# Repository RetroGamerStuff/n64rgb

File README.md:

# N64 RGB 

A collection of RGB mods for the N64. This repository includes:

- a simple RGB amp
  * based on TI's video amplifier THS7374 / THS7373 (only for some NTSC-units)
  * folder: simpleRGBAmp
- a general RGB digital-to-analog converter based on viletims schematics
  * supported devices: MaxII (EPM240T100C5, EPM570T100C5) and MaxV (5M240ZT100C4, 5M570ZT100C4) CPLDs
  * PCB files (common for all supported devices) and firmware (separate programming files) are provided
  * folder: generalRGBmod
- an advanced RGB digital-to-analog converter with optional YPbPr conversion
  * supported FPGA: Cyclone IV EP4CE10E22 and Cyclone 10 LP 10CL010YE144
  * PCB files (common for all supported devices) and firmware (separate programming files) are provided
  * additional Filter board for the outputted video signal if you need that
  * folder: advancedRGBmod
- additional RCP-NUS Adapter (flexible PCB):
  * buffering of video signals for N64RGB/N64Adv installs with wires
  * PCB files provided
  * folder: misc/RCP2Pads
- additional RCP-NUS to N64RGBv2.1/N64Adv install adapter (long flexible PCB):
  * buffering of video signals for N64RGBv2.1/N64Adv
  * can be directly connected to modding board
  * PCB files provided
  * folder: misc/RCP2N64RGB
- Filter AddOn for N64RGBv2 and N64 Advanced:
  * used to filter the video signal comming out of the ADV7125 or to adjust signal levels such that one can use SNES PAL RGB cables
  * PCB files provided
  * folder: misc/FilterAddOn
- Filter AddOn as flexible PCB for N64RGBv2.1 and N64 Advanced:
  * used to filter the video signal comming out of the ADV7125 or to adjust signal levels such that one can use SNES PAL RGB cables
  * PCB files provided
  * folder: misc/N64RGB2MoutFilter
- additional power supply PCB for viletime N64RGB DAC and N64RGBv1
  * PCB files provided
  * folder: misc/PowerReg

## Acknowledgement

Of course, many thanks to viletim for his initial CPLD-based DAC project, for providing a valuable commercial modding board as well as for publishing the schematics and source codes for that project.
I also want to send many thanks to Ikari_01. He has written the code to detect 480i and PAL/NTSC output with the CPLD. He provides a source code for the XC9572XL, which can be accessed here: [URL to Ikari_01's GitHub repository](https://github.com/mrehkopf/n64rgb)
Last but not least, thank you to Bob for his website [RetroRGB](http://retrorgb.com) and especially in this context here for collecting and sharing all the [RGB information regarding the N64](http://retrorgb.com/n64.html).

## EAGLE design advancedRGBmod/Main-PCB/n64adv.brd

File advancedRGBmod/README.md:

# Advanced N64 RGB Digital-to-Analog Mod

This folder contains all you need for a complete DIY RGB mod.

Please don't ask me for selling a modding. I either sell some prototypes on some forums marketplaces (which is very unlikely) or I don't have any of the boards.
This is a complete DIY modding project. So everybody is on his own here.

**WARNING:** This is an advanced DIY project if you do everything on your own. You need decent soldering skills. The FPGA has 0.5mm fine pitch with 144pins and one exposed pad below the IC, which has to be soldered to the PCB. Next to it the video DAC has also 0.5mm pin pitch on the board there are some SMD1206 resistor and ferrit bead arrays.

## Features

- Supporting for different FPGAs [1] on a common PCB design:
  * Cyclone IV EP4CE10E22
  * Cyclone 10 LP 10CL010YE144
- Video DAC ADV7125 (or ADV7123)
- Detection of 240p/288p vs. 480i/576i together with detection of NTSC vs. PAL mode
- VI-DeBlur in 240p/288p (horizontal resolution decreased from 640 to 320 pixels)
- 15bit color mode
- IGR features:
  * reset the console with the controller
  * full control on de-blur and 15bit mode with the controller
- Advanced features:
  * output of RGsB or YPBPr on demand
  * linedoubling of 240p/288p video to 480p/576p
  * linetrippling of 240p to (pseudo) 720p (NTSC content only, generated resolution is not a standard resolution so compatibility highly depends on your TV)
  * Bob de-interlace of 480i/576i to 480p/576p (with optional field shift fix (reduces vertical flicker))
  * configurable hybrid scanlines
  * Dejitter for PAL in LineX2 mode [2]
  * possible VGA output [3]
  * on-screen menu for configuration

The following shortly describes the main features of the firmware and how to use / control them.

#### Notes
##### [1]
For now, support for 6k LEs FPGAs (EP4CE6E22 and 10CL006YE144) has been discontinued. They are to small for an OSD menu implementation due to the small amount of block RAM. I will try to get it fit in future.

##### [2]

Experimental feature which might not be compatible with all PAL games. Please report incompatibilities on GitHub!

##### [3]

Not available if the filter adddon is used as HSYNC and VSYNC are shared outputs with F1 and F2 (filter selection)

### In-Game Routines (IGR)

Three functunalities are implemented: toggle de-blur feature / override heuristic for de-blur and toggle the 15bit mode (see above) as well as resetting the console.

The button combination are as follows:

- open on-screen menu: D-pad ri + L + R + C-ri
- reset the console: Z + Start + R + A + B (must be enabled in menu)
- (de)activate vi-deblur: (must be enabled in menu, see description above)
  - deactivate: Z + Start + R + C-le
  - activate: Z + Start + R + C-ri
- (de)activate 15bit mode: (must be enabled in menu, see description above)
  - deactivate: Z + Start + R + C-up
  - activate: Z + Start + R + C-dw

_Final remark on IGR_:  
However, as the communication between N64 and the controller goes over a single wire, sniffing the input is not an easy task (and probably my solution is not the best one). This together with the lack of an exhaustive testing (many many games out there as well my limited time), I'm looking forward to any incomming issue report to furhter improve this feature :)

### LowRes.-Deblur (VI-DeBlur)

VI-DeBlur of the picture information is only performed in 240p/288p. This is be done by simply blanking every second pixel. Normally, the blanked pixels are used to introduce blur by the N64 in 240p/288p mode. However, some games like Mario Tennis, 007 Goldeneye, and some others use these pixel for additional information rather than for blurring effects. In other words this means that these games uses full horizontal resolution even in 240p/288p output mode. Hence, the picture looks more blurry in this case if vi-deblur feature is activated.

The default state (whether vi-deblur is enabled for 240p/288p content or not) can be set in the menu.

### 16bit Color Mode

The 16bit color mode reduces the color depth from 21bit (7bit for each color) downto 16bits (5bit for red and blue, 6bit for green). Some very few games processes the color information in 16bit. The 16bit color mode simply sets LSBs to '0'.

- By default the 16bit mode is *off*! The default is set on each power cycle but not on a reset. Default can be switched in menu.
- to deactivate 16bit mode press Z + Start + R + C-up. (quick access function must be enabled in menu)
- to (re)activate 16bit mode press Z + Start + R + C-dw. (quick access function must be enabled in menu)

### Low Pass Filtering of the Video Output

The video DAC does not use any filtering. In general, this is also not needed. If you need DAC post-filtering though (receiver has a ADC build without any pre-filtering), you can install the filter addon (also provided in this repository).

The filter addon is based on a THS7368, where the video channels with selectable filter are used. As the filter is selected over the same pins as HSYNC and VSYNC, the addon is not compatible to VGA.

## Technical Information

A complete installation and setup guide to this modding kit is provided in the main folder of the repository. Here are some additional short notes.

### Checklist: How to build the project

- Use PCB files to order your own PCB or simply use the shared project(s) on OSHPark
- Source the components you need, e.g. from Mouser or Digikey
- Wait for everything to arrive
- Assemble your PCB
- Set all jumpers
- Flash the firmware to the serial flash device either in advanced (e.g. using the MiniPro) or after installation (e.g. using an Altera USB Blaster)
  * In advanced:
    * use the n64adv\__fpga-device_\_spi.bin binary
    * If your programmer does not support the serial flash  device on the N64Adv board (currently IS25LP016D), you may setup the flash program for another compatible device (e.g. A25L016 @SOP8). You may have to uncheck _Check ID_ options (or similar)
  * After installing:
    * Use the JIC programming file named n64adv\__fpga-device_.jic
    * Using the IntelFPGA programmer, JTAG chain is initialized by loading JIC file
    * N64 needs to be powered for flashing
    * Power cycle the N64 after flashing

### Jumpers

**IMPORTANT NOTE**  
Most jumpers are used as fallback if the software is unable to load a valid configuration from flash device U5. They were introduced on the modding board before a menu was in the firmware.  
The only exception is J1.2 - this jumper is still used to show the software whether the _Filter AddOn_ is installed or not.

There are some jumpers spreaded over the PCB, namely _J1_, _J2_, _J3_, _J4_, _J5_ and _J6_. _J1 - J4_ have to parts, let's say _.1_ and _.2_, where _.1_ is marked with the _dot_ on the PCB.

#### J1 (Filter AddOn)
##### J1.1 
- opened: output HSYNC and VSYNC for possible VGA output
- closed: use filter addon

##### J1.2
- opened: use filter of the addon board
- closed: bypass filter (actually filter is set to 95MHz cut-off which is way above the video signal content)

#### J2 (RGB, RGsB, YPbPr)
##### J2.1
- opened: RGB output
- closed: RGsB output (sync on green)

##### J2.2
- opened: RGB / RGsB output
- closed: YPbPr output (beats J2.1)

#### J3 (Scanline)
##### J3.1/J3.2
- opened / opened: 0%
- opened / closed: 25%
- closed / opened: 50%
- closed / closed: 100%

#### J33 (CSYNC level @ _/CS (75ohm)_ pad)

- opened: appr. 1.87V @ 75ohm termination i.e. needs a resistor inside the sync wire further attenuating the signal. Designed to work for cables with 470 ohm resistor inside resulting in appr. 450mV @ 75ohm termination
- closed: appr. 300mV @ 75ohm termination suitable for pass through wired cables at sync, works with standard TV / scaler setup

#### J4 (Linemode)
##### J4.1
- opened: linedoubling of 240p/288p to 480p/576p
- closed: no-linedoubling (beats J4.2)

##### J4.2
- opened: no bob de-interlace of 480i/576i
- closed: bob de-interlace of 480i/576i to 480p/576p (J4.1 must be opened)

#### J5
_J5_ is the JTAG connector.

#### J6 (_Outdated_; Power supply of analog outputs)
The analog part can be power with **either** 3.3V **or** 5V. If you want to power this part of the PCB with 3.3V, close _J6_ and leave pad _5V_ unconnected. If you want to power this part with 5V, leave _J6_ opened and connect pad _5V_ to +5V power rail of the N64. **NEVER connect 5V and close J6.**

#### Fallback Mode

A fallback mode can be activated by holding reset button down while powering on the N64. In the fallback mode **linedoubling and component conversion is turned off**. Sync on G/Y output is still on if one J2.1 or J2.2 is set as it does not affect RGBS.

### Source the PCB

Choose the PCB service which suits you. Here are some:

- OSHPark: [Link to the Main PCB](https://oshpark.com/shared_projects/Xo6yoQwD) (If the PCB was updated and I forgot to update this link, look onto [my profile](https://oshpark.com/profiles/borti4938))
- PCBWay.com: [Link](http://www.pcbway.com/), [Affiliate Link](http://www.pcbway.com/setinvite.aspx?inviteid=10658)

### Part List for the PCB

This part list a recommendation how the PCB is designed. If you are able to find pin-compatible devices / parts, you can use them.

#### Components

Components are listed in advancedRGBmod/Main-PCB/BOM_n64advanced.xlsx

### Firmware
The firmware is located in the folder firmware/. To build the firmware on your own you need Quartus Prime Lite (any version which supports Cyclone IV and 10 LP devices).

If you only want to flash the firmware, the configuration files are pre-compiled and located in firmware/output_files. You need the JIC appropriate for the FPGA you opted for (look for the *\_extension*).

For flashing you need:

- Altera USB Blaster
- Standalone Quartus Prime Programmer and Tools

#### Firmware Revision Numbering

- 1.0: initially commited version
- 2.0 (HDL) / 1.0 (SW): initial version with OSD driven menu
- HDL got a fallback to v. 1.xx from 2.0 after a while

#### Road Map / New Ideas

- return of vi-deblur heuristic
- test screen
- some more menu stuff

Any other ideas: email me :)

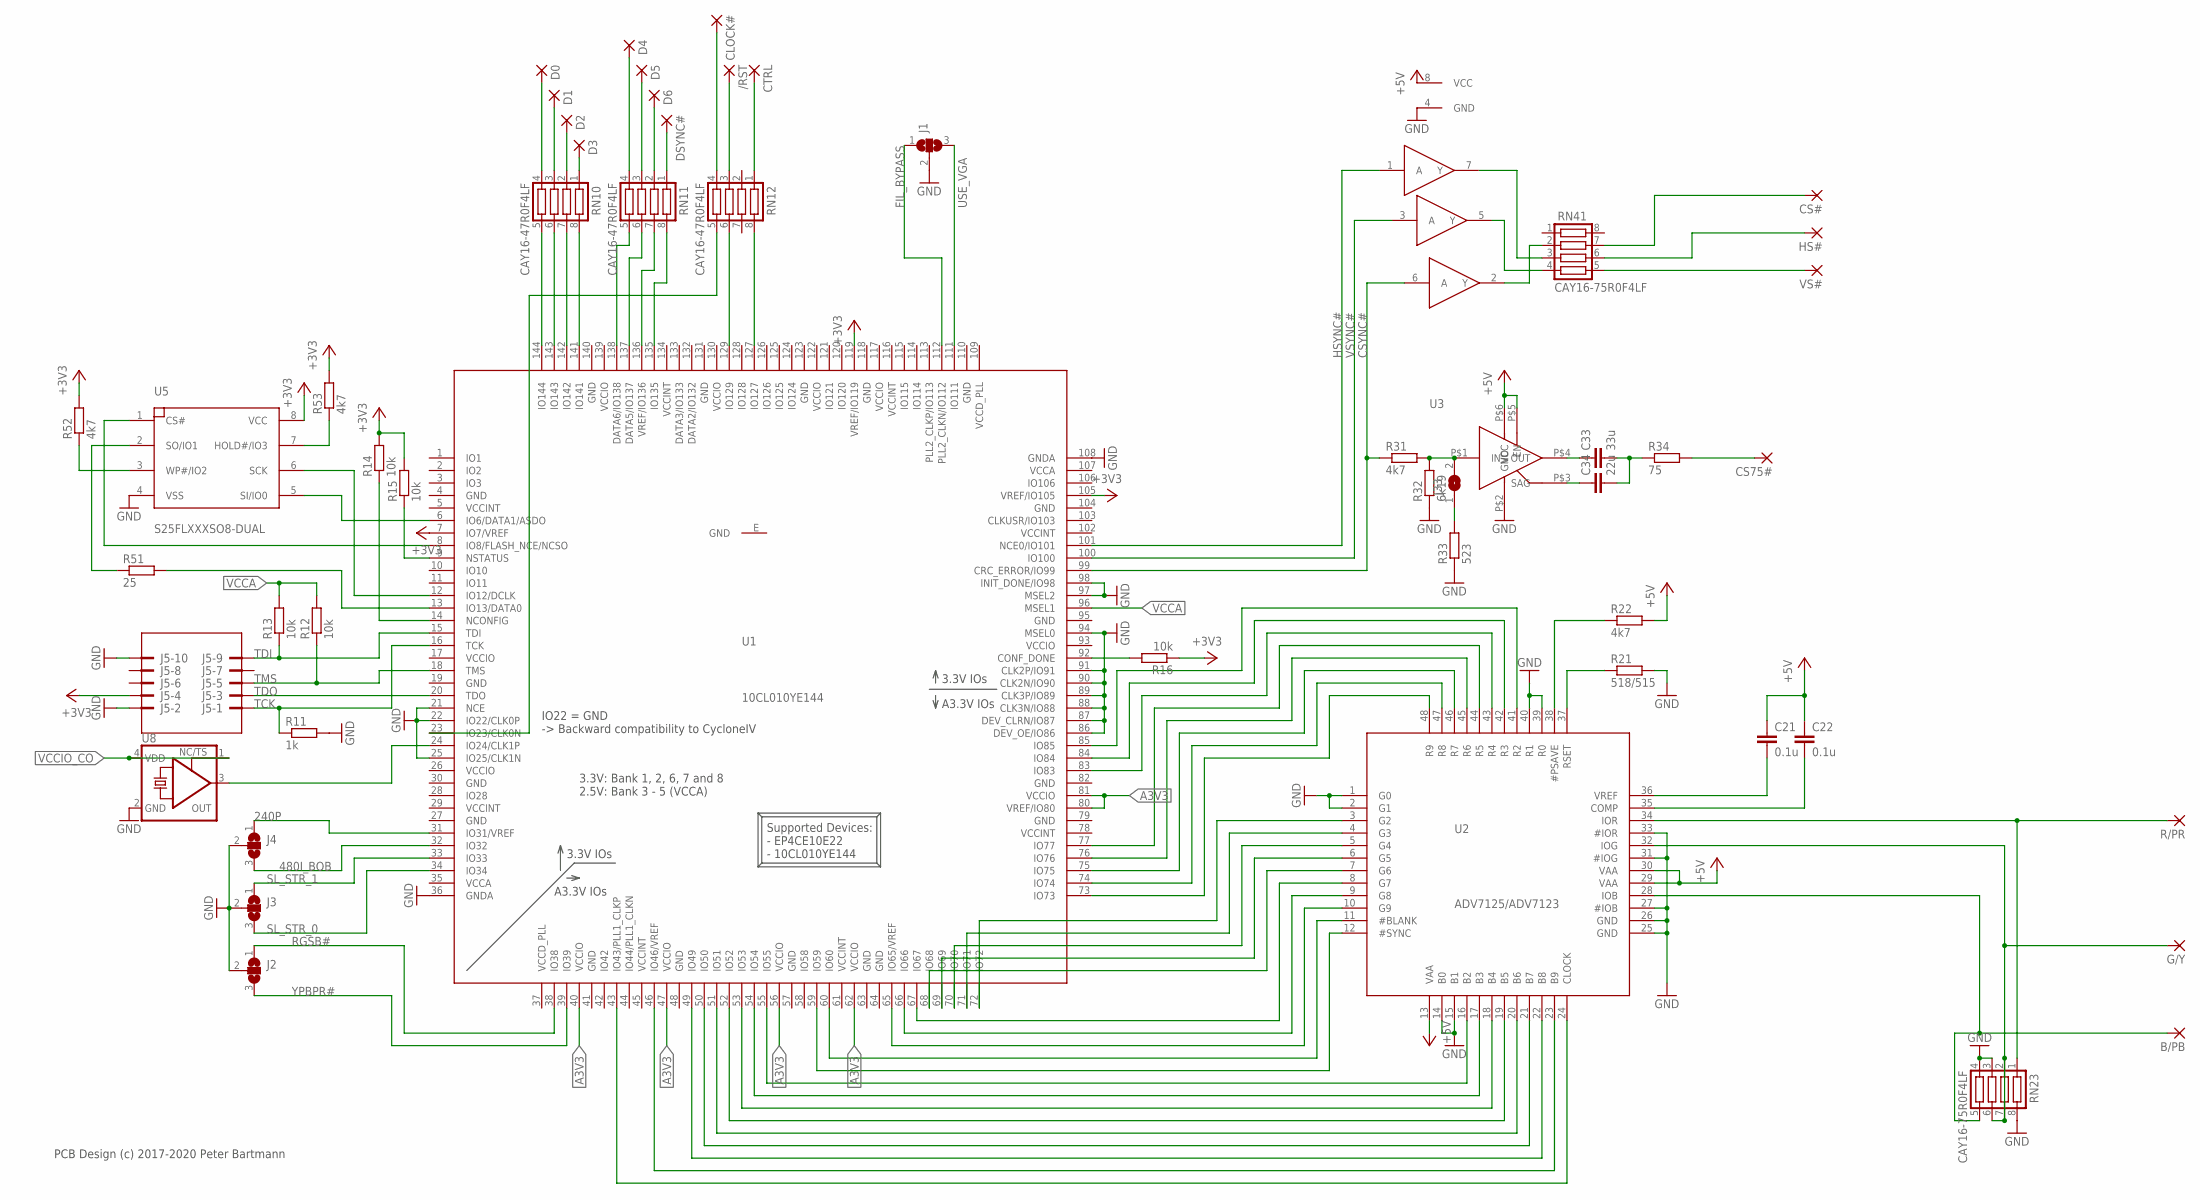
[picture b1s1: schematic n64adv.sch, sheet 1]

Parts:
/RST: SMD1; SMD0,8-1,6
B/PB: SMD2; SMD1,27-2,54
C21, C22: 0.1u; C0603
C33: 33u; C0805
C34: 22u; C0805
CLOCK#: SMD1; SMD0,8-1,6
CS75#: SMD2; SMD1,27-2,54
CS#: SMD2; SMD1,27-2,54
CTRL: SMD1; SMD0,8-1,6
D0, D1, D2, D3, D4, D5, D6: SMD1; SMD0,8-1,6
DSYNC#: SMD1; SMD0,8-1,6
G/Y: SMD2; SMD1,27-2,54
HS#: SMD2; SMD1,27-2,54
J1, J2, J3, J4: SJ2W; SJ_2
J5: 2510-; PAK100/2500-10
J33: SJ
R11: 1k; R0603
R12, R13, R14, R15, R16: 10k; R0603
R21: 518/515; R0603
R22, R31, R52, R53: 4k7; R0603
R32: 6k19; R0603
R33: 523; R0603
R34: 75; R0603
R51: 25; R0603
R/PR: SMD2; SMD1,27-2,54
RN10, RN11, RN12: CAY16-47R0F4LF; CTS742C083
RN23, RN41: CAY16-75R0F4LF; CTS742C083
U1: 10CL010YE144; EQFP144_2
U2: ADV7125/ADV7123; LQFP48
U3: TSH122ICT; SC70
U4: 74LVC3G17; 74LVC3G34
U5: S25FLXXXSO8-DUAL; SO8-DUAL
U8: KXO-PXO/XO-V96; 3.2X2.5_KXO-V96
VS#: SMD2; SMD1,27-2,54

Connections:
240P: J4.1, U1.31 (IO31/VREF)
480I_BOB: J4.3, U1.32 (IO32)
+5V: C21.1, C22.1, R22.2, U2.13 (VAA), U2.29 (VAA), U2.30 (VAA), U3.P$5 (EN), U3.P$6 (VCC), U4.8 (VCC); also elsewhere on the board
A3V3: U1.40 (VCCIO), U1.47 (VCCIO), U1.56 (VCCIO), U1.62 (VCCIO), U1.80 (VREF/IO80), U1.81 (VCCIO); also elsewhere on the board
BLUE: B/PB.1, RN23.5, U2.28 (IOB)
CSYNC47#: CS#.1, RN41.7
CSYNC#: R31.1, U1.99 (CRC_ERROR/IO99), U4.6 (A)
FIL_BYPASS: J1.1, U1.112 (PLL2_CLKN/IO112)
GND: J1.2, J2.2, J3.2, J4.2, J5.2, J5.10, R11.2, R21.2, R32.1, R33.1, RN23.3, RN23.4, RN23.8, U1.4 (GND), U1.19 (GND), U1.21 (NCE), U1.22 (IO22/CLK0P), U1.25 (IO25/CLK1N), U1.27 (GND), U1.30 (GND), U1.36 (GNDA), U1.41 (GND), U1.48 (GND), U1.57 (GND), U1.63 (GND), U1.64 (GND), U1.79 (GND), U1.82 (GND), U1.86 (DEV_OE/IO86), U1.87 (DEV_CLRN/IO87), U1.88 (CLK3N/IO88), U1.89 (CLK3P/IO89), U1.90 (CLK2N/IO90), U1.91 (CLK2P/IO91), U1.94 (MSEL0), U1.95 (GND), U1.97 (MSEL2), U1.98 (INIT_DONE/IO98), U1.104 (GND), U1.108 (GNDA), U1.110 (GND), U1.118 (GND), U1.123 (GND), U1.131 (GND), U1.140 (GND), U1.E (GND), U2.1 (G0), U2.2 (G1), U2.14 (B0), U2.15 (B1), U2.25 (GND), U2.26 (GND), U2.27 (#IOB), U2.31 (#IOG), U2.33 (#IOR), U2.39 (R0), U2.40 (R1), U3.P$2 (GND), U4.4 (GND), U5.4 (VSS), U8.2 (GND); also elsewhere on the board
GREEN: G/Y.1, RN23.2, RN23.6, RN23.7, U2.32 (IOG)
HSYNC47#: HS#.1, RN41.6
HSYNC#: U1.101 (NCE0/IO101), U4.1 (A)
unnamed: J33.2, R31.2, R32.2, U3.P$1 (IN)
unnamed: R21.1, U2.37 (RSET)
unnamed: RN12.5, U1.23 (IO23/CLK0N)
unnamed: U1.43 (IO43/PLL1_CLKP), U2.24 (CLOCK)
unnamed: U1.46 (IO46/VREF), U2.23 (B9)
unnamed: U1.49 (IO49), U2.22 (B8)
unnamed: U1.50 (IO50), U2.21 (B7)
unnamed: R14.1, U1.14 (NCONFIG)
unnamed: U1.51 (IO51), U2.20 (B6)
unnamed: U1.52 (IO52), U2.19 (B5)
unnamed: U1.53 (IO53), U2.18 (B4)
unnamed: U1.54 (IO54), U2.17 (B3)
unnamed: U1.55 (IO55), U2.16 (B2)
unnamed: U1.72 (IO72), U2.3 (G2)
unnamed: C33.1, U3.P$4 (OUT)
unnamed: C34.1, U3.P$3 (SAG)
unnamed: C33.2, C34.2, R34.1
unnamed: U1.71 (IO71), U2.4 (G3)
unnamed: U1.70 (IO70), U2.5 (G4)
unnamed: U1.69 (IO69), U2.6 (G5)
unnamed: CS75#.1, R34.2
unnamed: R22.1, U2.38 (#PSAVE)
unnamed: C22.2, U2.35 (COMP)
unnamed: C21.2, U2.36 (VREF)
unnamed: RN41.2, U4.2 (Y)
unnamed: U1.68 (IO68), U2.7 (G6)
unnamed: U1.67 (IO67), U2.8 (G7)
unnamed: U1.66 (IO66), U2.9 (G8)
unnamed: U1.65 (IO65/VREF), U2.10 (G9)
unnamed: U1.60 (IO60), U2.11 (#BLANK)
unnamed: U1.59 (IO59), U2.12 (#SYNC)
unnamed: U1.85 (IO85), U2.41 (R2)
unnamed: U1.84 (IO84), U2.42 (R3)
unnamed: U1.83 (IO83), U2.43 (R4)
unnamed: U1.77 (IO77), U2.44 (R5)
unnamed: U1.76 (IO76), U2.45 (R6)
unnamed: U1.75 (IO75), U2.46 (R7)
unnamed: U1.74 (IO74), U2.47 (R8)
unnamed: U1.73 (IO73), U2.48 (R9)
unnamed: RN10.5, U1.144 (IO144)
unnamed: RN10.6, U1.143 (IO143)
unnamed: RN10.7, U1.142 (IO142)
unnamed: RN10.8, U1.141 (IO141)
unnamed: R15.1, U1.9 (NSTATUS)
unnamed: RN11.5, U1.138 (DATA6/IO138)
unnamed: RN41.4, U4.5 (Y)
unnamed: RN11.6, U1.137 (DATA5/IO137)
unnamed: RN11.7, U1.136 (VREF/IO136)
unnamed: RN11.8, U1.135 (IO135)
unnamed: R16.2, U1.92 (CONF_DONE)
unnamed: D0.P$1, RN10.4
unnamed: RN12.6, U1.129 (IO129)
unnamed: R53.1, U5.7 (HOLD#/IO3)
unnamed: RN12.8, U1.127 (IO127)
unnamed: D1.P$1, RN10.3
unnamed: D2.P$1, RN10.2
unnamed: D3.P$1, RN10.1
unnamed: D4.P$1, RN11.4
unnamed: D5.P$1, RN11.3
unnamed: D6.P$1, RN11.2
unnamed: DSYNC#.P$1, RN11.1
unnamed: CLOCK#.P$1, RN12.4
unnamed: CTRL.P$1, RN12.1
unnamed: R52.1, U5.3 (WP#/IO2)
unnamed: RN41.3, U4.7 (Y)
unnamed: R51.1, U5.2 (SO/IO1)
unnamed: /RST.P$1, RN12.3
unnamed: J33.1, R33.2
unnamed: R51.2, U1.13 (IO13/DATA0)
unnamed: U1.12 (IO12/DCLK), U5.6 (SCK)
unnamed: U1.8 (IO8/FLASH_NCE/NCSO), U5.1 (CS#)
unnamed: U1.6 (IO6/DATA1/ASDO), U5.5 (SI/IO0)
unnamed: U1.24 (IO24/CLK1P), U8.3 (OUT)
RED: R/PR.1, RN23.1, U2.34 (IOR)
RGSB#: J2.1, U1.38 (IO38)
SL_STR_0: J3.3, U1.34 (IO34)
SL_STR_1: J3.1, U1.33 (IO33)
TCK: J5.1, R11.1, U1.16 (TCK)
TDI: J5.9, R13.1, U1.15 (TDI)
TDO: J5.3, U1.20 (TDO)
TMS: J5.5, R12.1, U1.18 (TMS)
USE_VGA: J1.3, U1.111 (IO111)
VCCA: R12.2, R13.2, U1.35 (VCCA), U1.96 (MSEL1), U1.107 (VCCA); also elsewhere on the board
VCCD_PLL: U1.37 (VCCD_PLL), U1.109 (VCCD_PLL); also elsewhere on the board
VCCINT: U1.5 (VCCINT), U1.29 (VCCINT), U1.45 (VCCINT), U1.61 (VCCINT), U1.78 (VCCINT), U1.102 (VCCINT), U1.116 (VCCINT), U1.134 (VCCINT); also elsewhere on the board
VCCIO: J5.4, R14.2, R15.2, R16.1, R52.2, R53.2, U1.7 (IO7/VREF), U1.17 (VCCIO), U1.26 (VCCIO), U1.93 (VCCIO), U1.105 (VREF/IO105), U1.117 (VCCIO), U1.119 (VREF/IO119), U1.122 (VCCIO), U1.130 (VCCIO), U1.139 (VCCIO), U5.8 (VCC); also elsewhere on the board
VCCIO_CO: U8.1 (TS), U8.4 (VDD); also elsewhere on the board
VSYNC47#: RN41.5, VS#.1
VSYNC#: U1.100 (IO100), U4.3 (A)
YPBPR#: J2.3, U1.39 (IO39)

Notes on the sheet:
IO22 = GND -> Backward compatibility to CycloneIV
Supported Devices: - EP4CE10E22 - 10CL010YE144
PCB Design (c) 2017-2020 Peter Bartmann
3.3V: Bank 1, 2, 6, 7 and 8 2.5V: Bank 3 - 5 (VCCA)
3.3V IOs
A3.3V IOs

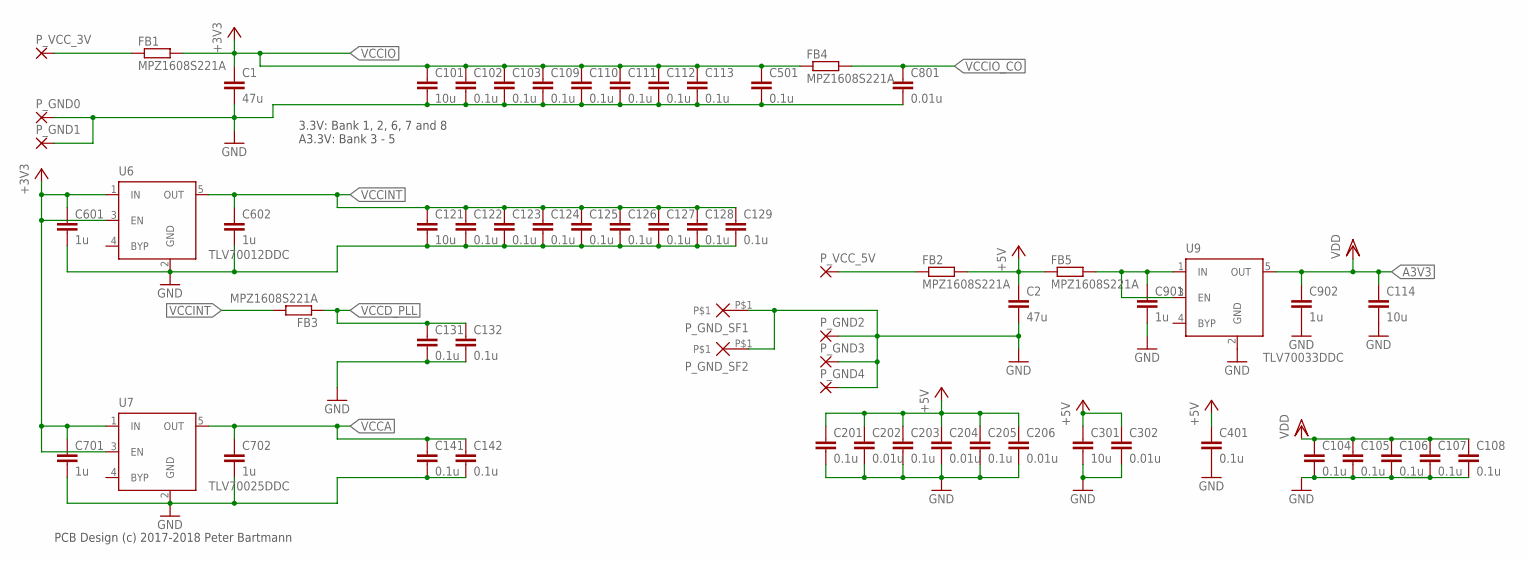
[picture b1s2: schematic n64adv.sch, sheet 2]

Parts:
C1, C2: 47u; C0805
C101, C114, C121, C301: 10u; C0805
C102, C103, C104, C105, C106, C107, C108, C109, C110, C111, C112, C113, C122, C123, C124, C125, C126, C127, C128, C129, C131, C132, C141, C142, C201, C203, C205, C401, C501: 0.1u; C0603
C202, C204, C206, C302, C801: 0.01u; C0603
C601, C602, C701, C702, C901, C902: 1u; C0603
FB1, FB2, FB3, FB4, FB5: MPZ1608S221A; R0603
P_GND0, P_GND1, P_GND2, P_GND3, P_GND4: SMD2; SMD1,27-2,54
P_GND_SF1, P_GND_SF2: PADSHIELD_FINGER; GND_FINGER_PAD
P_VCC_3V, P_VCC_5V: SMD2; SMD1,27-2,54
U6: TLV70012DDC; SOT23-5
U7: TLV70025DDC; SOT23-5
U9: TLV70033DDC; SOT23-5

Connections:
+5V: C2.1, C201.1, C202.1, C203.1, C204.1, C205.1, C206.1, C301.1, C302.1, C401.1, FB2.2, FB5.1; also elsewhere on the board
A3V3: C104.1, C105.1, C106.1, C107.1, C108.1, C114.1, C902.1, U9.5 (OUT); also elsewhere on the board
GND: C1.2, C2.2, C101.2, C102.2, C103.2, C104.2, C105.2, C106.2, C107.2, C108.2, C109.2, C110.2, C111.2, C112.2, C113.2, C114.2, C121.2, C122.2, C123.2, C124.2, C125.2, C126.2, C127.2, C128.2, C129.2, C131.2, C132.2, C141.2, C142.2, C201.2, C202.2, C203.2, C204.2, C205.2, C206.2, C301.2, C302.2, C401.2, C501.2, C601.2, C602.2, C701.2, C702.2, C801.2, C901.2, C902.2, P_GND0.1, P_GND1.1, P_GND2.1, P_GND3.1, P_GND4.1, P_GND_SF1.P$1, P_GND_SF2.P$1, U6.2 (GND), U7.2 (GND), U9.2 (GND); also elsewhere on the board
unnamed: C901.1, FB5.2, U9.1 (IN), U9.3 (EN)
unnamed: FB2.1, P_VCC_5V.1
unnamed: FB1.1, P_VCC_3V.1
VCCA: C141.1, C142.1, C702.1, U7.5 (OUT); also elsewhere on the board
VCCD_PLL: C131.1, C132.1, FB3.1; also elsewhere on the board
VCCINT: C121.1, C122.1, C123.1, C124.1, C125.1, C126.1, C127.1, C128.1, C129.1, C602.1, FB3.2, U6.5 (OUT); also elsewhere on the board
VCCIO: C1.1, C101.1, C102.1, C103.1, C109.1, C110.1, C111.1, C112.1, C113.1, C501.1, C601.1, C701.1, FB1.2, FB4.1, U6.1 (IN), U6.3 (EN), U7.1 (IN), U7.3 (EN); also elsewhere on the board
VCCIO_CO: C801.1, FB4.2; also elsewhere on the board

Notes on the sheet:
PCB Design (c) 2017-2018 Peter Bartmann
3.3V: Bank 1, 2, 6, 7 and 8 A3.3V: Bank 3 - 5

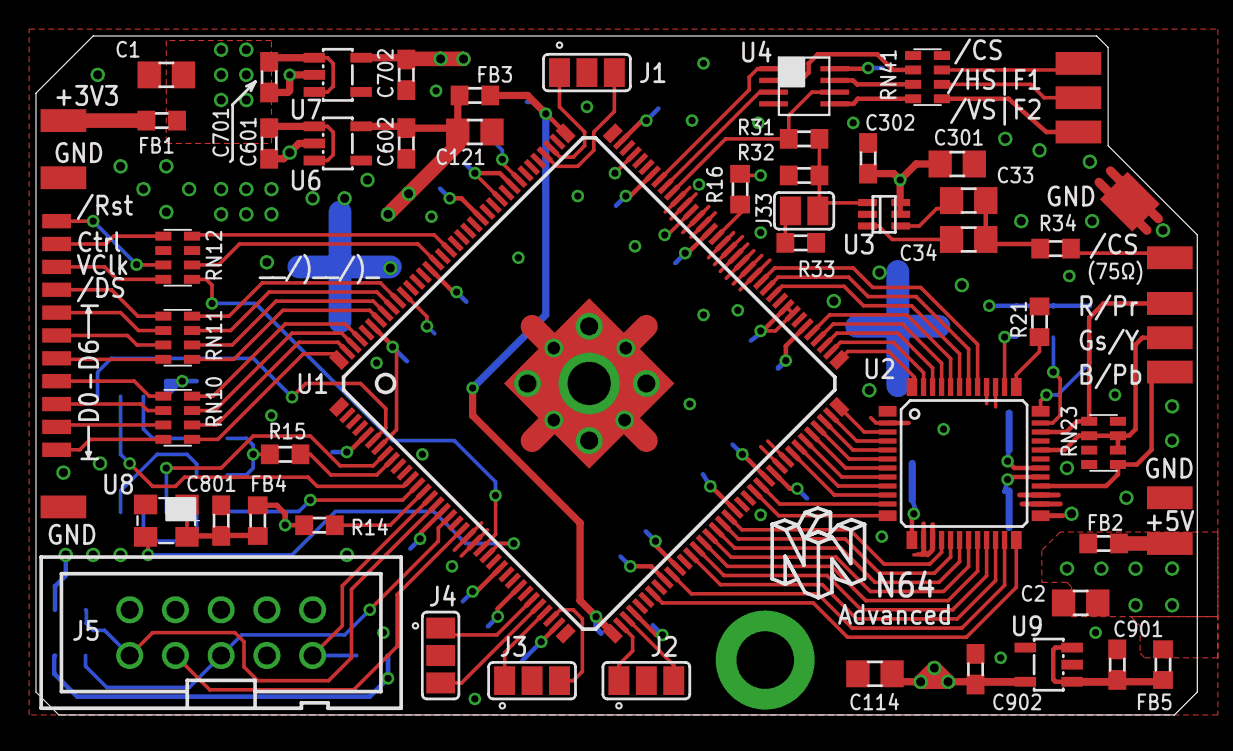
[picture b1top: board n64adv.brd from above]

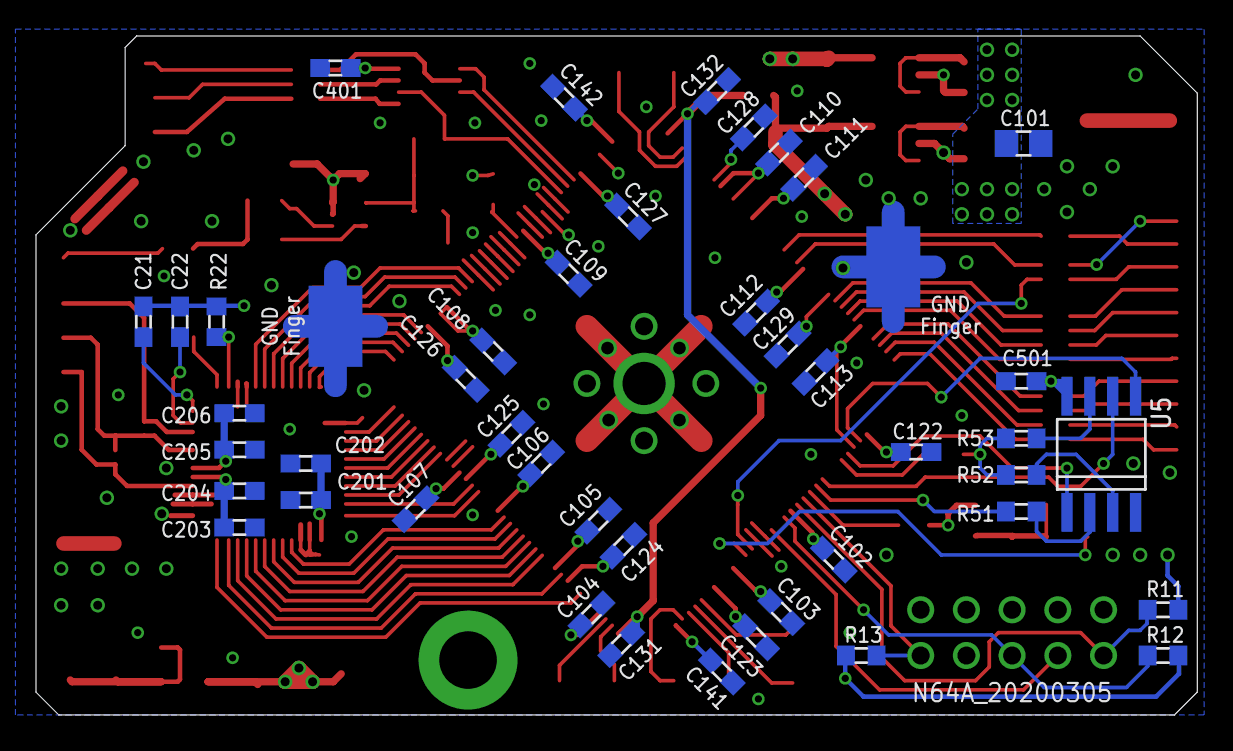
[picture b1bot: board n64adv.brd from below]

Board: 4 copper layers, 64.5 x 37.7 mm, 117 parts (45 on the bottom side), 105 nets.

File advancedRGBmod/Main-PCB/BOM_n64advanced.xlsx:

Designator | MPN | QTY | DESCRIPTION | VALUE | PACKAGE | NOTES | Digikey | Mouser
U1 | 10CL010YE144C8G | 1 | Cyclone 10 LP FPGA, 10k LE |  | EQFP144 | can be replaced with other FPGAs on demand (see Schematic file) | https://www.digikey.de/product-detail/de/intel-fpgas-altera/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 | https://www.mouser.de/ProductDetail/Intel-Altera/10CL010YE14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
U2 | ADV7125KSTZ140 | 1 | Video DAC 8bit, 3Ch. |  | 48-LQFP | can be replaced with ADV7123KSTZ140 on demand | https://www.digikey.de/product-detail/de/analog-devices-inc/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 | https://www.mouser.de/ProductDetail/Analog-Devices/ADV7125KS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
U3 | TSH122ICT | 1 | Video Verstärker 1Ch |  | SC-70-6 |  | https://www.digikey.de/product-detail/de/stmicroelectronics/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 | https://www.mouser.de/ProductDetail/STMicroelectronics/TSH12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
U4 | SN74LVC3G17DCTR | 1 | Non-Inv Buffer 3Ch., Schmitt Trigger |  | 8-LSSOP, 8-MSOP | TI: DCT Package Footprint | https://www.digikey.de/product-detail/de/texas-instruments/S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 | https://www.mouser.de/ProductDetail/Texas-Instruments/SN74LV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
U5 | IS25LP016D-JBLE-TR | 1 | IC FLASH 16MBIT 108MHZ 8SOIC |  | 8-SOIC | 208mil Body | https://www.digikey.de/product-detail/de/issi-integrated-sil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 | https://www.mouser.de/ProductDetail/870-IS25LP016DJBLETR
U6 | TLV70012DDCR | 1 | LDO 1.2V |  | SOT-23-5 |  | https://www.digikey.de/product-detail/de/texas-instruments/T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 | https://www.mouser.de/ProductDetail/Texas-Instruments/TLV700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
U7 | TLV70025DDCR | 1 | LDO 2.5V |  | SOT-23-5 |  | https://www.digikey.de/product-detail/de/texas-instruments/T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 | https://www.mouser.de/ProductDetail/Texas-Instruments/TLV700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
U8 | ASE-50.000MHZ-LC-T | 1 | OSC 50MHz | 50MHz | 4-SMD | L x B: 0,126" x 0,098" (3,20 mm x 2,50 mm) | https://www.digikey.de/product-detail/de/abracon-llc/ASE-50.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 | https://www.mouser.de/ProductDetail/ABRACON/ASE-50000MHZ-L-C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
C1,C2 | GRM219R60J476ME44D | 2 | Ceramic capacitor, X5R | 47uF / 6.3V | SMD0805 |  | https://www.digikey.de/product-detail/de/murata-electronics-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 | http://www.mouser.de/ProductDetail/Murata/GRM219R60J476ME44D/
C21,C22,C102,C103,C104,C105,C106,C107,C108,C109,C110,C111,C112,C113,C122,C123,C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 | GRM188R71H104KA93J | 31 | Ceramic capacitor, X7R | 0.1uF / 50V | SMD0603 |  | https://www.digikey.de/product-detail/de/murata-electronics-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 | http://www.mouser.de/ProductDetail/Murata/GRM188R71H104KA93J/
C101,C121,C301 | GRM21BR60J106ME19L | 3 | Ceramic capacitor, X5R | 10uF / 6.3V | SMD0805 |  | https://www.digikey.de/product-detail/de/murata-electronics-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 | http://www.mouser.de/ProductDetail/Murata/GRM21BR60J106ME19L/
C202,C204,C206,C302,C801 | GRM188R70J103KA01D | 5 | Ceramic capacitor, X7R | 0.01uF / 50V | SMD0603 |  | https://www.digikey.de/product-detail/de/murata-electronics-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 | http://www.mouser.de/ProductDetail/Murata/GRM188R70J103KA01D/
C33 | GRM32DR60J336ME19L | 1 | Ceramic capacitor, X5R | 33uF / 6.3V | SMD1210 |  | https://www.digikey.de/product-detail/de/murata-electronics-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 | http://www.mouser.de/ProductDetail/Murata-Electronics/GRM32D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
C34 | GRM31CR60J226KE19L | 1 | Ceramic capacitor, X5R | 22uF / 6.3V | SMD1206 |  | https://www.digikey.de/product-detail/de/murata-electronics-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 | http://www.mouser.de/ProductDetail/Murata/GRM31CR60J226KE19L/
C601,C602,C701,C702 | GRM18R60J105KA01J | 4 | Ceramic capacitor, X5R | 1uF / 6.3V | SMD0603 |  | https://www.digikey.de/product-detail/de/murata-electronics-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 | https://www.mouser.de/ProductDetail/Murata/GRM188R60J105KA01J/
FB1,FB2,FB3,FB4 | MPZ1608S221A | 4 | Ferrit bead, power line |  | SMD0603 |  | https://www.digikey.de/product-detail/de/tdk-corporation/MPZ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 | http://www.mouser.de/ProductDetail/TDK/MPZ1608S221A/
J5 | 30310-6002HB | 1 |  |  |  | JTAG Connector | https://www.digikey.de/product-detail/de/3m/30310-6002HB/303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 | http://www.mouser.de/ProductDetail/3M/30310-6002HB/
R11 | RC0603FR-071KL | 1 | Resistor | 1k | SMD0603 |  | https://www.digikey.de/product-detail/de/yageo/RC0603FR-071K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 | http://www.mouser.de/ProductDetail/Yageo/RC0603FR-071KL/
R12,R13,R14,R15,R16 | RC0603FR-0710KL | 5 | Resistor | 10k | SMD0603 |  | https://www.digikey.de/product-detail/de/yageo/RC0603FR-0710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 | http://www.mouser.de/ProductDetail/Yageo/RC0603FR-0710KL/
R21 | RC0603FR-07523RL | 1 | Resistor | 518 | SMD0603 | with ADV7123: use 516ohm resistor; for PAL-Standard: 528ohm/527ohm | https://www.digikey.de/product-detail/de/yageo/RC0603FR-0752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 | http://www.mouser.de/ProductDetail/Yageo/RC0603FR-07523RL/
R22,R31,R52,R53 | RC0603FR-074K7L | 4 | Resistor | 4k7 | SMD0603 |  | https://www.digikey.de/product-detail/de/yageo/RC0603FR-074K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 | http://www.mouser.de/ProductDetail/Yageo/RC0603FR-074K7L/
R32 | RC0603FR-07475RL | 1 | Resistor | 475 | SMD0603 |  | https://www.digikey.de/product-detail/de/yageo/RC0603FR-0747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 | http://www.mouser.de/ProductDetail/Yageo/RC0603FR-07475RL/
R33 | RC0603FR-0775RL | 1 | Resistor | 75 | SMD0603 |  | https://www.digikey.de/product-detail/de/yageo/RC0603FR-0775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 | http://www.mouser.de/ProductDetail/Yageo/RC0603FR-0775RL/
R51 | RC0603FR-0724R9L | 1 | Resistor | 25 | SMD0603 |  | https://www.digikey.de/product-detail/de/yageo/RC0603FR-0724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 | http://www.mouser.de/ProductDetail/Yageo/RC0603FR-0724R9L/
RN10,RN11,RN12 | CAT16-47R0F4LF | 3 | Resistor Array (4x) | 47 | SMD1206 | Alternative: CAY16-47R0F4LF | https://www.digikey.de/product-detail/de/bourns-inc/CAT16-47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 | http://www.mouser.de/ProductDetail/Bourns/CAT16-47R0F4LF/
RN23,RN41 | CAT16-75R0F4LF | 2 | Resistor Array (4x) | 75 | SMD1206 | Alternative: CAY16-75R0F4LF; Digi-Key Link zur J4LF Serie (5% Toleranz statt 1%) | https://www.digikey.de/product-detail/de/bourns-inc/CAT16-75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 | http://www.mouser.de/search/ProductDetail.aspx?R=0virtualkey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

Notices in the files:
advancedRGBmod/firmware/software/n64adv2/controller_app/menu_text/textdefs_p.h:
Copyright (C) 2016-2018 by Peter Bartmann <borti4938@gmx.de>
N64 RGB/YPbPr DAC is free software: you can redistribute it and/or modify
it under the terms of the GNU General Public License as published by
the Free Software Foundation, either version 3 of the License, or
any later version.
advancedRGBmod/Main-PCB/n64adv2.brd:
PCB (c) 2018 by Peter Bartmann aka borti4938
misc/N64RGB2MoutFilter/n64rgb2moutfilter_nutzen.brd:
Flex-PCB (c) 2019, 2020 Peter Bartmann
